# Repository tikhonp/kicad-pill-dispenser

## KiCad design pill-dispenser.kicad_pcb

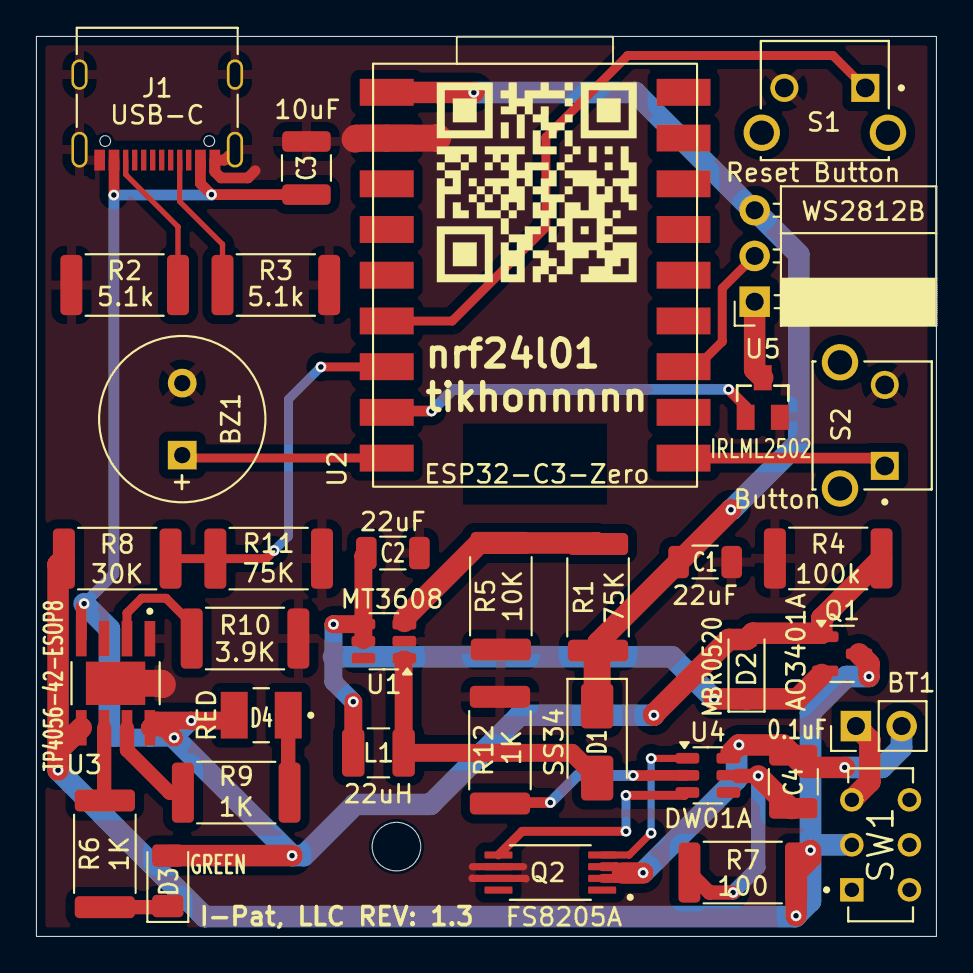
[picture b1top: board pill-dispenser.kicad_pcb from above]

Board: 2 copper layers, 50.0 x 50.0 mm, 36 parts (0 on the bottom side), 27 nets.

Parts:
BT1: Battery_Cell; PinHeader_1x02_P2.54mm_Vertical
BZ1: Buzzer; MagneticBuzzer_PUI_AT-0927-TT-6-R
C1, C2: 22uF; C_1206_3216Metric
C3: 10uF; C_1210_3225Metric
C4: 0.1uF; C_1210_3225Metric
D1: SS34; D_SMA
D2: MBR0520; D_SOD-123
D3: GREEN; LED_1206_3216Metric
D4: RED; LED_LG_T671-L2N1-1-Z
J1: USB-C; USB_C_Receptacle_Palconn_UTC16-G
J3: WS2812B; PinSocket_1x03_P2.54mm_Horizontal
L1: 22uH; L_1210_3225Metric
Q1: AO3401A; SOT-23
Q2: FS8205A; SOP65P640X120-8N
R1: 75К; R_2512_6332Metric
R2, R3: 5.1k; R_2512_6332Metric
R4: 100k; R_2512_6332Metric
R5: 10K; R_2512_6332Metric
R6, R9, R12: 1K; R_2512_6332Metric
R7: 100; R_2512_6332Metric
R8: 30K; R_2512_6332Metric
R10: 3.9K; R_2512_6332Metric
R11: 75K; R_2512_6332Metric
S1: Reset Button; SW_FSMRA6JH
S2: Button; SW_FSMRA6JH
SW1: Battery Switch; SW_EG1271
U1: MT3608; SOT-23-6
U2: ESP32-C3-Zero; Waveshare-ESP32-C3-Zero
U3: TP4056-42-ESOP8; SOIC127P600X175-9N
U4: DW01A; SOT-23-6
U5: IRLML2502; SOT23
qr: LOGO

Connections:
+5V: C1.1, D1.1 (K), J3.3, R1.1, U2.1 (VCC)
/BAT_MON: R8.1, R11.1, U2.7 (IO3)
/BUTTON: S2.1, U2.10 (IO6)
/BUZ: BZ1.1 (+), U2.9 (IO5)
/LED_STRIP_CONTROL: J3.2, U2.12 (IO8)
/LED_STRIP_ENABLE: U2.8 (IO4), U5.1
/WAKEUP_BUT: S1.1, U2.6 (IO2)
GND: BZ1.2 (-), C1.2, C2.2, C3.2, J1.A1 (GND), J1.A12 (GND), J1.B1 (GND), J1.B12 (GND), J1.S1 (SHIELD), Q2.6, Q2.7, R2.1, R3.1, R4.2, R5.2, R10.1, R11.2, R12.2, S1.2, S2.2, U1.2 (GND), U2.2 (GND), U3.1 (TEMP), U3.3 (GND), U3.9 (EXP), U5.2
unnamed: BT1.1 (+), SW1.3
unnamed: BT1.2 (-), C4.2, Q2.2, Q2.3, U4.6 (GND)
unnamed: D1.2 (A), L1.2, U1.1 (SW)
unnamed: C2.1, D2.1 (K), L1.1, Q1.2 (S), U1.4 (EN), U1.5 (IN)
unnamed: D3.1 (K), R6.1
unnamed: D4.1 (K), R9.1
unnamed: J1.A5 (CC1), R3.2
unnamed: J1.B5 (CC2), R2.2
unnamed: J3.1, U5.3
unnamed: R1.2, R5.1, U1.3 (FB)
unnamed: R10.2, U3.2 (PROG)
unnamed: R9.2, U3.7 (~CHRG)
unnamed: R6.2, U3.6 (~STDBY)
unnamed: R12.1, U4.2 (CS)
unnamed: Q2.5, U4.3 (OC)
unnamed: Q2.4, U4.1 (OD)
unnamed: C4.1, R7.1, U4.5 (VCC)
VBAT: Q1.3 (D), R7.2, R8.2, SW1.2, U3.5 (BAT)
VUSB: C3.1, D2.2 (A), D3.2 (A), D4.2 (A), J1.A4 (VBUS), J1.A9 (VBUS), J1.B4 (VBUS), J1.B9 (VBUS), Q1.1 (G), R4.1, U3.4 (VCC), U3.8 (CE)

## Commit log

2025-06-18 Created pill-dispenser schematic
2025-06-19 Finished schematic
2025-06-25 Finished schematic and prepare for PCB layout
2025-06-25 Created PCB layout
2025-06-25 Updated pcb after exporting
2025-06-25 Created 3D model
2025-06-26 Fixed errors in PCB layout
2025-06-26 Updated PCB to REV1.1 version
2025-06-26 Uodated rev 1.1
2025-07-09 Working on 1.2 final version
2025-07-10 Updated pcb to rev1.2
2025-08-04 Updated BOM export rules
2025-08-25 Added control led strip transotor, placed buttons on PCB
2025-08-25 Fixed transitor silkscreen font size
2025-08-26 Added prepare gerbers script
